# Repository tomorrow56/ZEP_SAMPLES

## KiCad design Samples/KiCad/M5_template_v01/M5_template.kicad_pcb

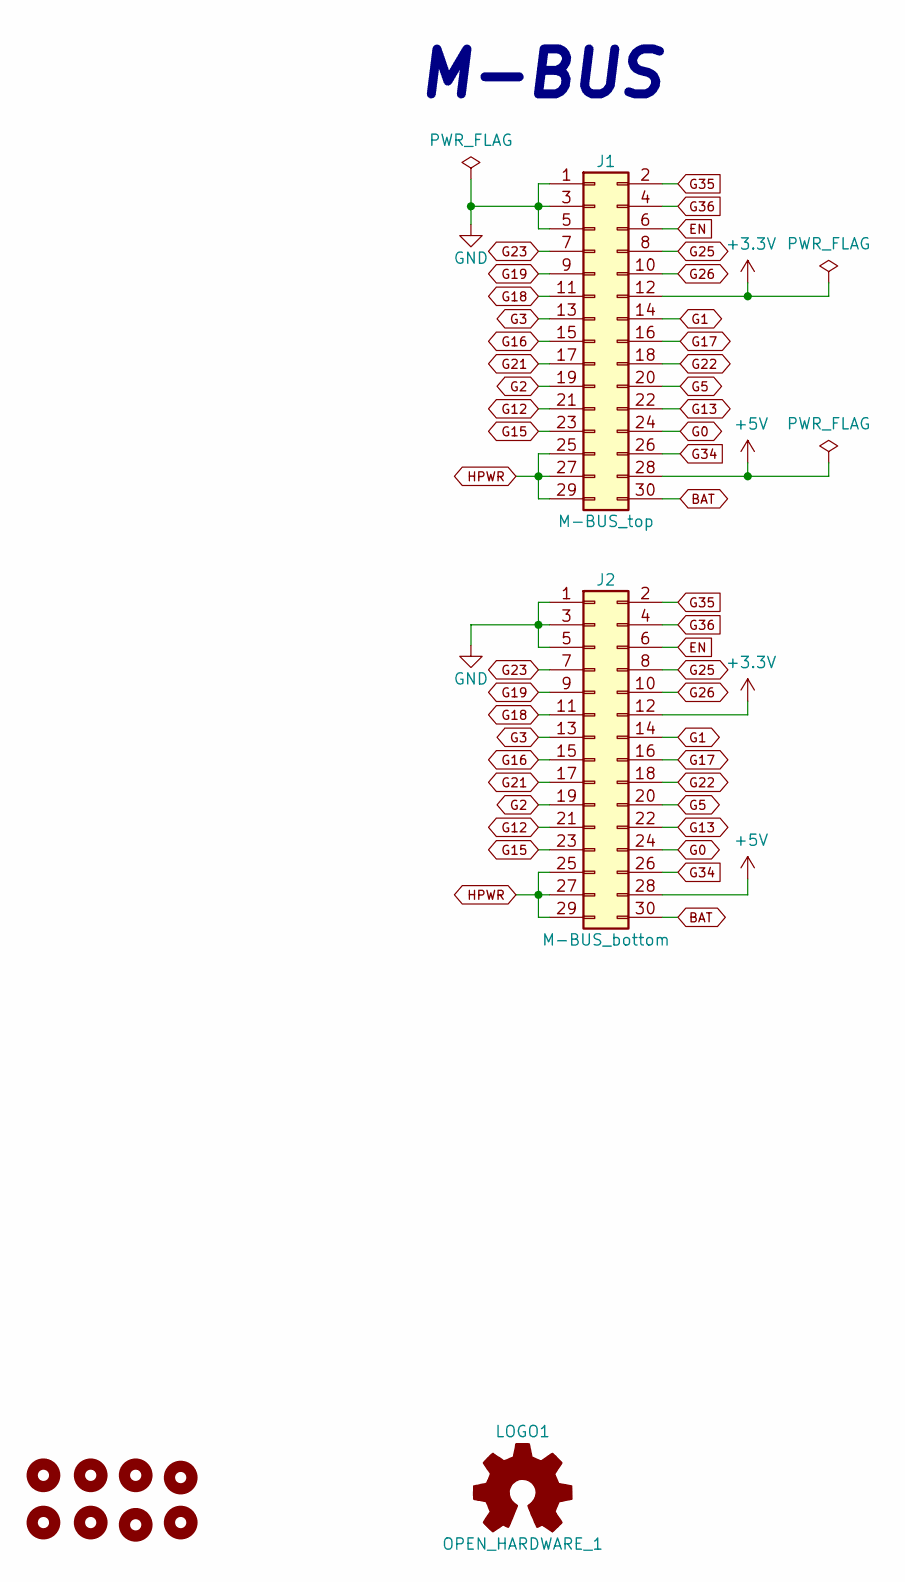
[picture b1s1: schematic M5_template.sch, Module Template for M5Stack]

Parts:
J1: M-BUS_top; Pin_Header_MBUS_SMD_top
J2: M-BUS_bottom; Pin_Header_MBUS_SMD_bottom
LOGO1: OPEN_HARDWARE_1; OSHW-Logo_5.7x6mm_SilkScreen
MK1, MK2, MK3, MK4: Mounting_Hole; MountingHole_M3_mod
MK5, MK6, MK7, MK8: Mounting_Hole; MountingHole_M2_mod

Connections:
+3V3: J1.12, J2.12
+5V: J1.28, J2.28
BAT: J1.30, J2.30
EN: J1.6, J2.6
G0: J1.24, J2.24
G1: J1.14, J2.14
G2: J1.19, J2.19
G3: J1.13, J2.13
G5: J1.20, J2.20
G12: J1.21, J2.21
G13: J1.22, J2.22
G15: J1.23, J2.23
G16: J1.15, J2.15
G17: J1.16, J2.16
G18: J1.11, J2.11
G19: J1.9, J2.9
G21: J1.17, J2.17
G22: J1.18, J2.18
G23: J1.7, J2.7
G25: J1.8, J2.8
G26: J1.10, J2.10
G34: J1.26, J2.26
G35: J1.2, J2.2
G36: J1.4, J2.4
GND: J1.1, J1.3, J1.5, J2.1, J2.3, J2.5
HPWR: J1.25, J1.27, J1.29, J2.25, J2.27, J2.29

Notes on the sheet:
M-BUS

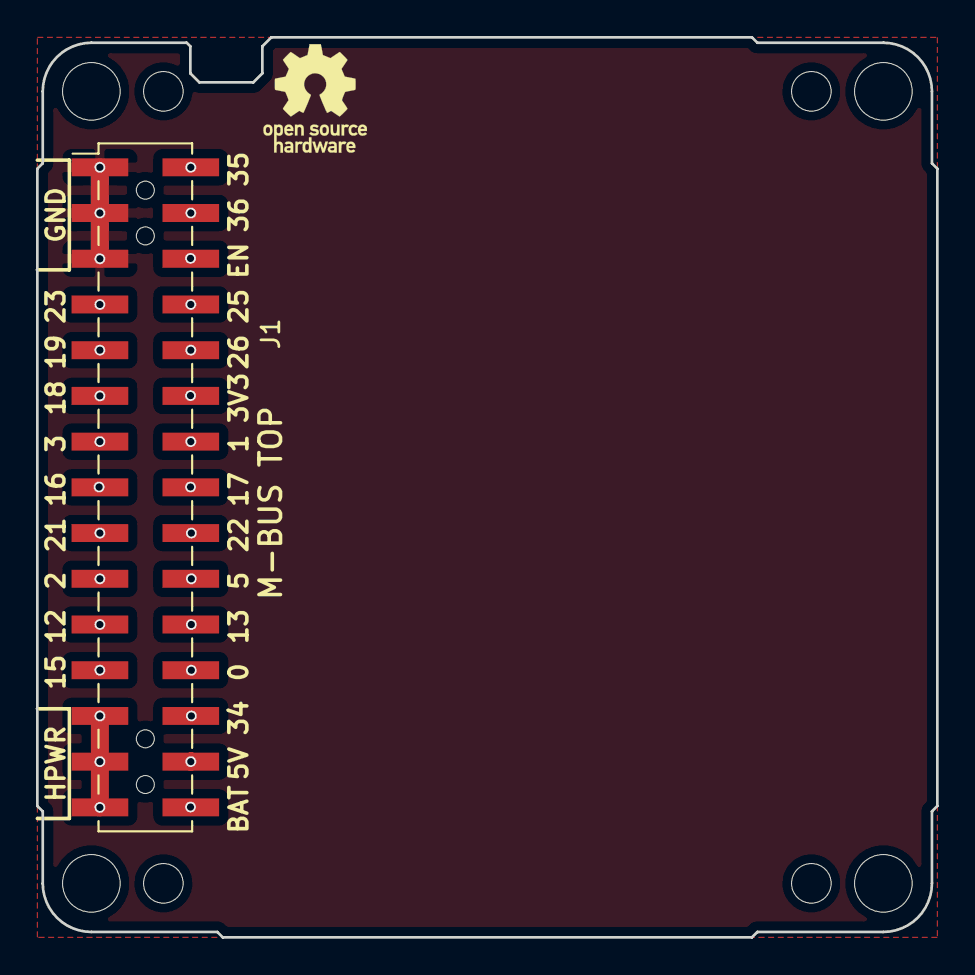
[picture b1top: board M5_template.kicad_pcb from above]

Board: 2 copper layers, 50.0 x 50.0 mm, 11 parts (0 on the bottom side), 26 nets.
